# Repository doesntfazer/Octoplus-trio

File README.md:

# Octoplus-trio
 11 key one handed artsey/ardux keyboard

Left handed versions are tested and working.

Firmware is in the firmware folder.

Right handed versions have not been tested, but should work.

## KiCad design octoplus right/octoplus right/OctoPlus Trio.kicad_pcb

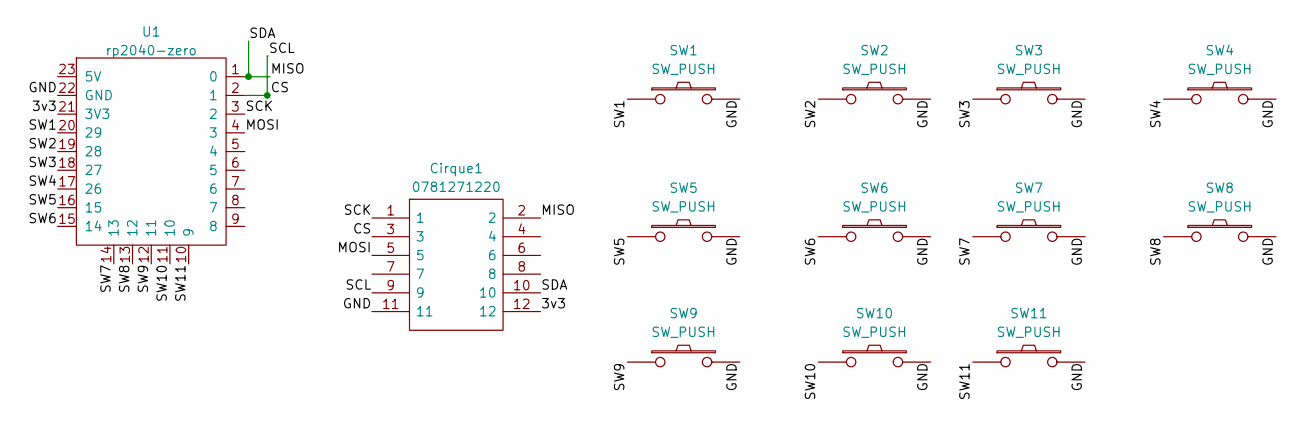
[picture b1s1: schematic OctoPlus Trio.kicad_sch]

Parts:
Cirque1: 0781271220; Mouser Part Number 538-78127-1220
SW1, SW2, SW3, SW4, SW5, SW6, SW7, SW8, SW9, SW10, SW11: SW_PUSH; Kailh_socket_MX
U1: rp2040-zero; rp2040-zero-tht-nocut

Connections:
/3v3: Cirque1.12, U1.21 (3V3)
/CS: Cirque1.3, Cirque1.9, U1.2 (1)
/GND: Cirque1.11, SW1.2, SW2.2, SW3.2, SW4.2, SW5.2, SW6.2, SW7.2, SW8.2, SW9.2, SW10.2, SW11.2, U1.22 (GND)
/MISO: Cirque1.2, Cirque1.10, U1.1 (0)
/MOSI: Cirque1.5, U1.4 (3)
/SCK: Cirque1.1, U1.3 (2)
/SW1: SW1.1, U1.20 (29)
/SW2: SW2.1, U1.19 (28)
/SW3: SW3.1, U1.18 (27)
/SW4: SW4.1, U1.17 (26)
/SW5: SW5.1, U1.16 (15)
/SW6: SW6.1, U1.15 (14)
/SW7: SW7.1, U1.14 (13)
/SW8: SW8.1, U1.13 (12)
/SW9: SW9.1, U1.12 (11)
/SW10: SW10.1, U1.11 (10)
/SW11: SW11.1, U1.10 (9)

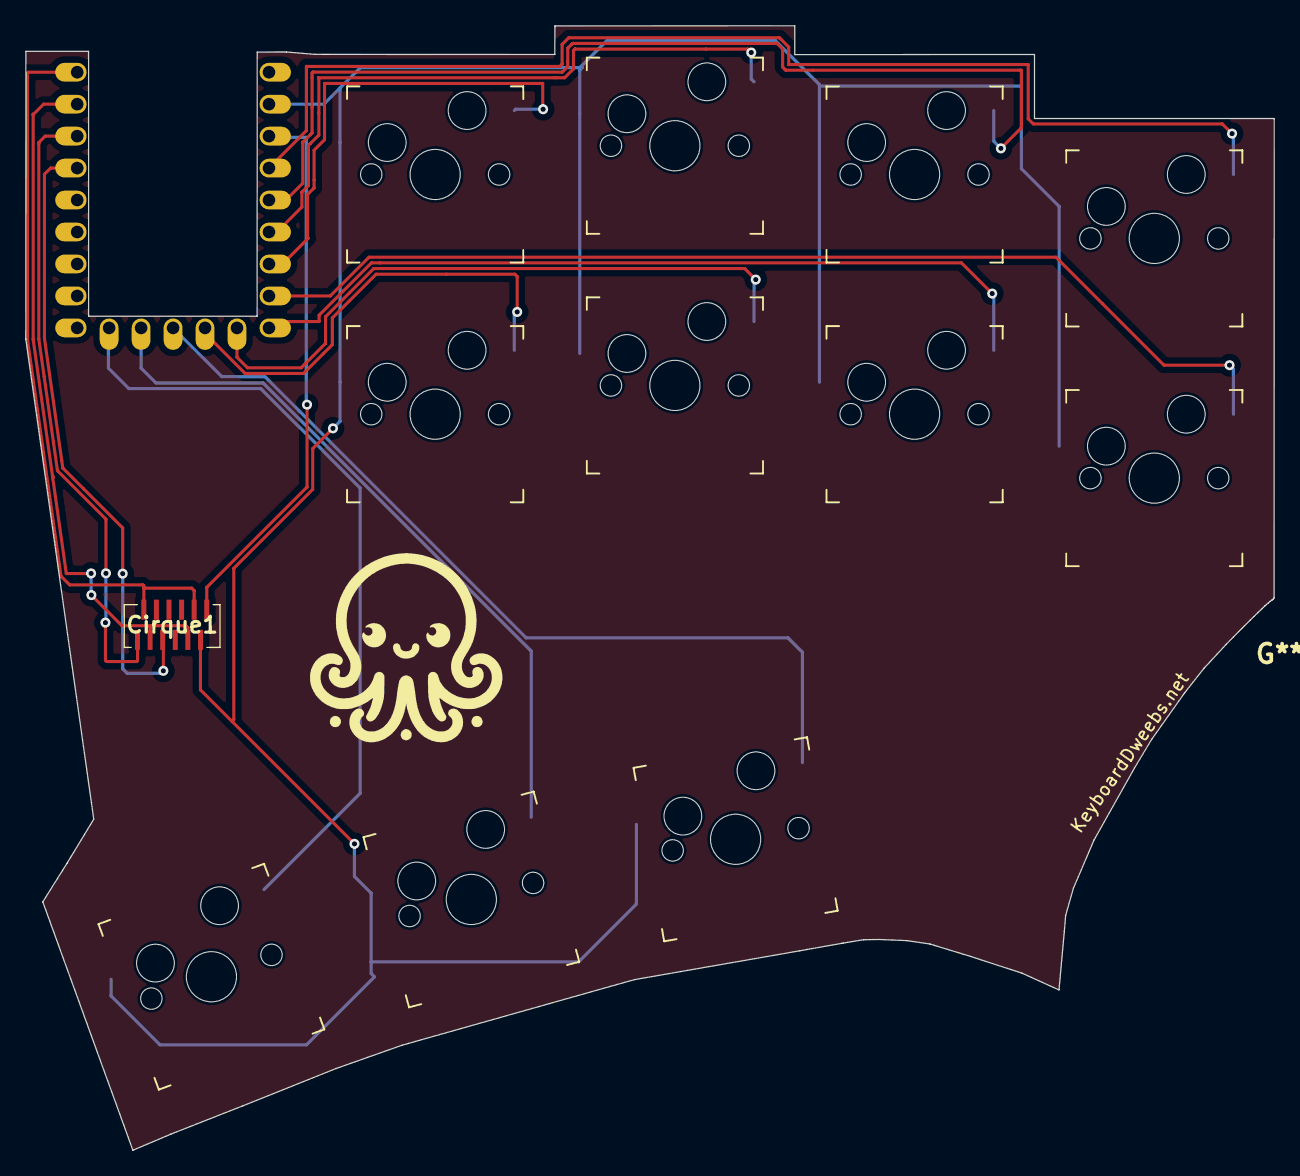
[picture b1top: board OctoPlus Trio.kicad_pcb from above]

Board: 2 copper layers, 99.2 x 89.4 mm, 13 parts (1 on the bottom side), 17 nets.

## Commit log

2024-02-15 first pr left handed
2024-02-20 adding right handed version
2024-02-20 Commit Firmware
2024-02-20 Reorganized
2024-02-20 placeholder
